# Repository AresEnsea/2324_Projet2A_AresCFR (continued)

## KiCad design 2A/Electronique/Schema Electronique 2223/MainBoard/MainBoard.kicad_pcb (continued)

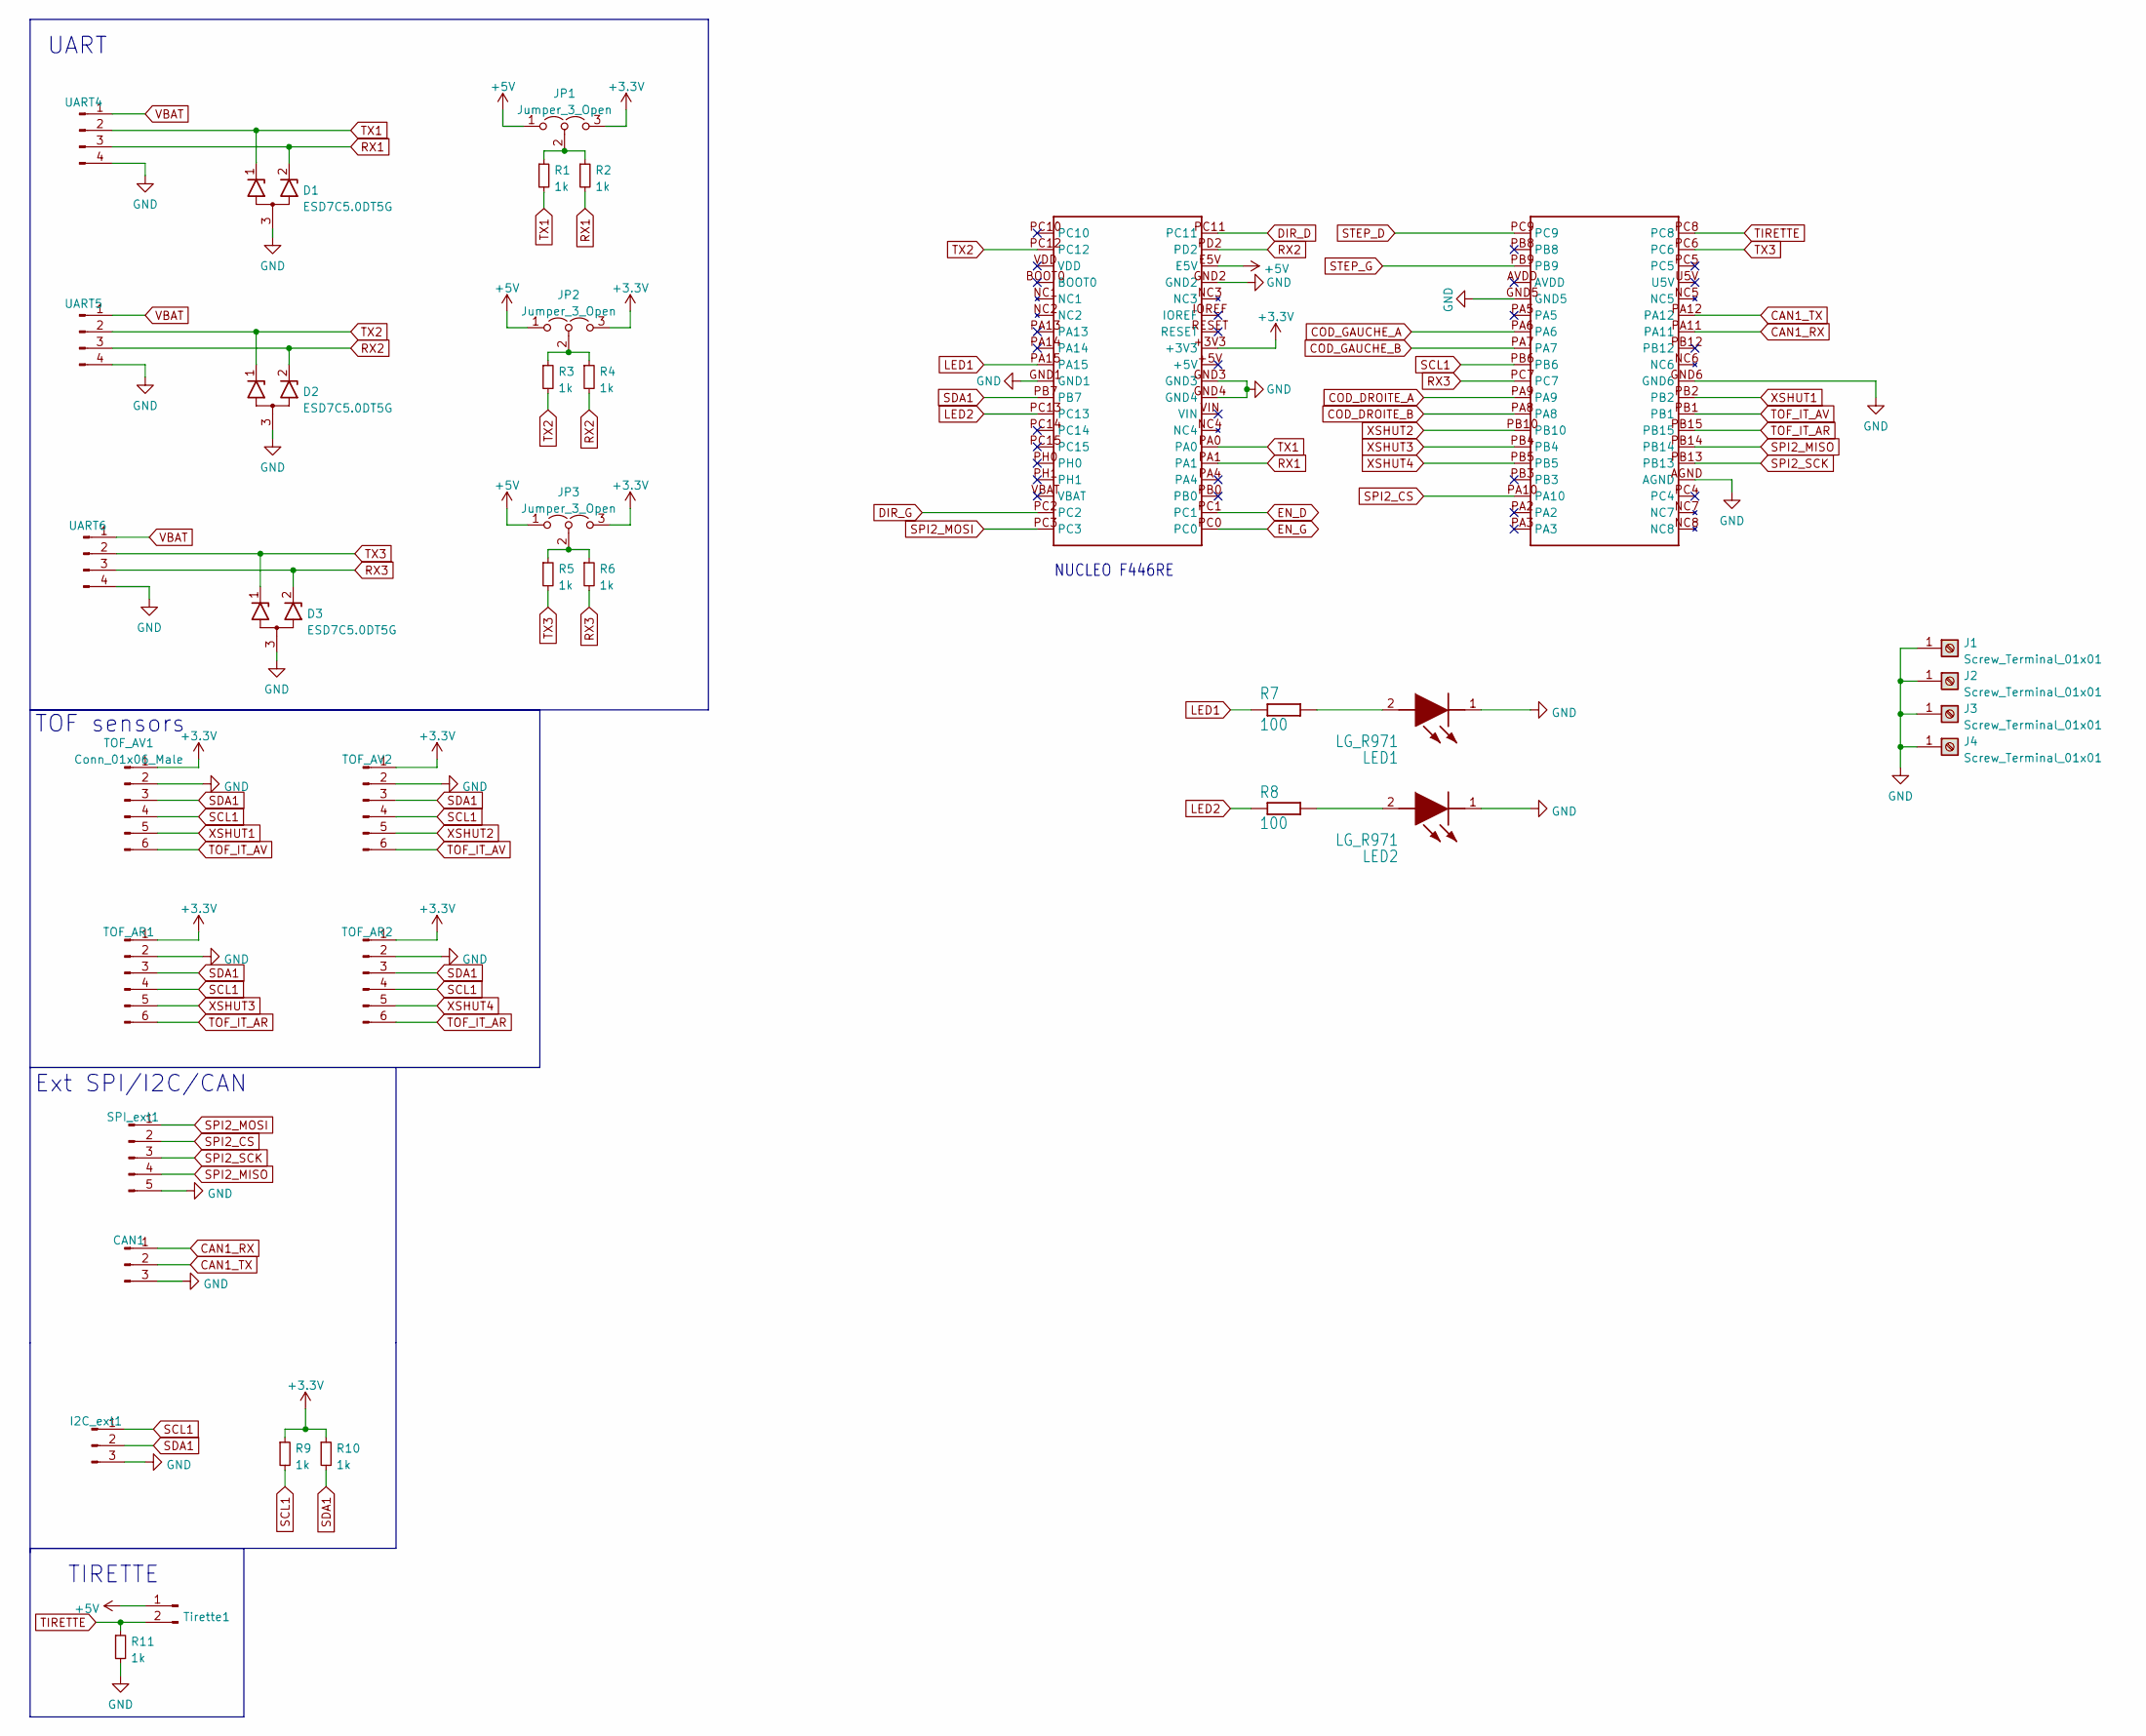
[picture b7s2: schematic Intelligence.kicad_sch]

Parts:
CAN1: Conn_01x03_Male; JST_XH_B3B-XH-A_1x03_P2.50mm_Vertical
D1, D2, D3: ESD7C5.0DT5G; SOT-416; Mouser Part Number 863-ESD7C5.0DT5G
I2C_ext1: Conn_01x03_Male; JST_XH_B3B-XH-A_1x03_P2.50mm_Vertical
J1, J2, J3, J4: Screw_Terminal_01x01; MountingHole_4.3mm_M4_ISO7380_Pad
JP1, JP2, JP3: Jumper_3_Open; PinHeader_1x03_P2.54mm_Vertical
LED1, LED2: LG_R971; LEDC2012X90N
R1, R2, R3, R4, R5, R6, R9, R10, R11: 1k; R_0805_2012Metric_Pad1.20x1.40mm_HandSolder
R7, R8: 100; R0805
SPI_ext1: Conn_01x05_Male; JST_XH_B5B-XH-A_1x05_P2.50mm_Vertical
TOF_AR1, TOF_AR2: Conn_01x06_Male; JST_XH_B6B-XH-A_1x06_P2.50mm_Vertical
TOF_AV1, TOF_AV2: Conn_01x06_Male; JST_XH_B6B-XH-A_1x06_P2.50mm_Vertical
Tirette1: Conn_01x02_Male; PinHeader_1x02_P2.54mm_Vertical
U1: NUCLEO_F446RE; MB1136
UART4, UART5, UART6: Conn_01x04_Male; JST_XH_B4B-XH-A_1x04_P2.50mm_Vertical

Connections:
+3.3V: JP1.3 (B), JP2.3 (B), JP3.3 (B), R9.1, R10.1, TOF_AR1.1, TOF_AR2.1, TOF_AV1.1, TOF_AV2.1, U1.+3V3
+5V: JP1.1 (A), JP2.1 (A), JP3.1 (A), Tirette1.1, U1.E5V; also elsewhere on the board
CAN1_RX: CAN1.1, U1.PA11
CAN1_TX: CAN1.2, U1.PA12
COD_DROITE_A: U1.PA9; also elsewhere on the board
COD_DROITE_B: U1.PA8; also elsewhere on the board
COD_GAUCHE_A: U1.PA6; also elsewhere on the board
COD_GAUCHE_B: U1.PA7; also elsewhere on the board
DIR_D: U1.PC11; also elsewhere on the board
DIR_G: U1.PC2; also elsewhere on the board
EN_D: U1.PC1; also elsewhere on the board
EN_G: U1.PC0; also elsewhere on the board
GND: CAN1.3, D1.3 (A), D2.3 (A), D3.3 (A), I2C_ext1.3, J1.1, J2.1, J3.1, J4.1, LED1.1 (K), LED2.1 (K), R11.2, SPI_ext1.5, TOF_AR1.2, TOF_AR2.2, TOF_AV1.2, TOF_AV2.2, U1.AGND, U1.GND1, U1.GND2, U1.GND3, U1.GND4, U1.GND5, U1.GND6, UART4.4, UART5.4, UART6.4; also elsewhere on the board
LED1: R7.1, U1.PA15
LED2: R8.1, U1.PC13
unnamed: JP1.2 (C), R1.1, R2.1
unnamed: JP2.2 (C), R3.1, R4.1
unnamed: JP3.2 (C), R5.1, R6.1
unnamed: LED1.2 (A), R7.2
unnamed: LED2.2 (A), R8.2
RX1: D1.2 (K2), R2.2, U1.PA1, UART4.3
RX2: D2.2 (K2), R4.2, U1.PD2, UART5.3
RX3: D3.2 (K2), R6.2, U1.PC7, UART6.3
SCL1: I2C_ext1.1, R9.2, TOF_AR1.4, TOF_AR2.4, TOF_AV1.4, TOF_AV2.4, U1.PB6
SDA1: I2C_ext1.2, R10.2, TOF_AR1.3, TOF_AR2.3, TOF_AV1.3, TOF_AV2.3, U1.PB7
SPI2_CS: SPI_ext1.2, U1.PA10
SPI2_MISO: SPI_ext1.4, U1.PB14
SPI2_MOSI: SPI_ext1.1, U1.PC3
SPI2_SCK: SPI_ext1.3, U1.PB13
STEP_D: U1.PC9; also elsewhere on the board
STEP_G: U1.PB9; also elsewhere on the board
TIRETTE: R11.1, Tirette1.2, U1.PC8
TOF_IT_AR: TOF_AR1.6, TOF_AR2.6, U1.PB15
TOF_IT_AV: TOF_AV1.6, TOF_AV2.6, U1.PB1
TX1: D1.1 (K1), R1.2, U1.PA0, UART4.2
TX2: D2.1 (K1), R3.2, U1.PC12, UART5.2
TX3: D3.1 (K1), R5.2, U1.PC6, UART6.2
VBAT: UART4.1, UART5.1, UART6.1; also elsewhere on the board
XSHUT1: TOF_AV1.5, U1.PB2
XSHUT2: TOF_AV2.5, U1.PB10
XSHUT3: TOF_AR1.5, U1.PB4
XSHUT4: TOF_AR2.5, U1.PB5

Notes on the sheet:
UART
NUCLEO F446RE
Ext SPI/I2C/CAN
TOF sensors
TIRETTE

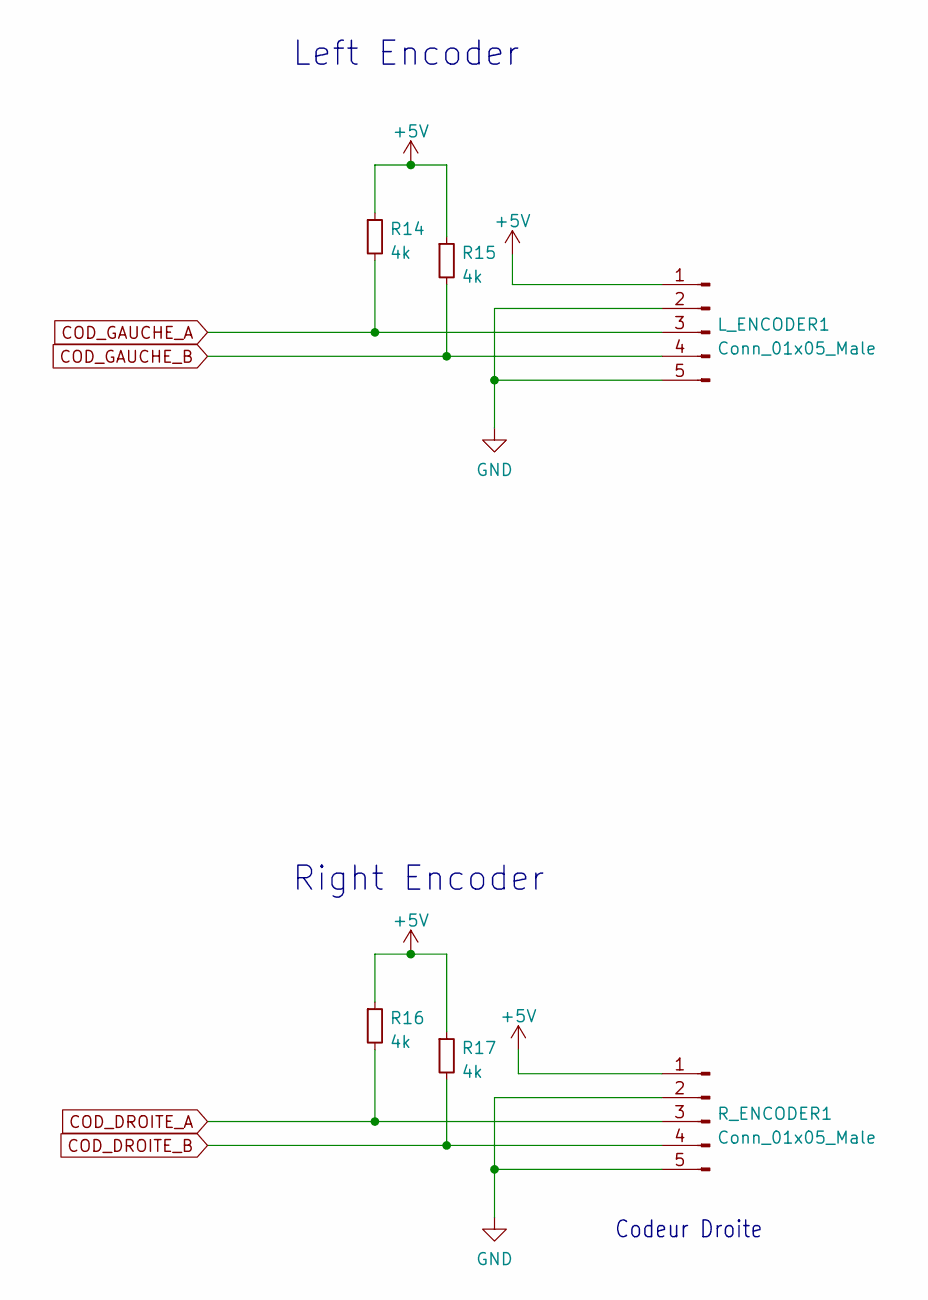
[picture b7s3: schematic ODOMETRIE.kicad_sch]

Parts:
L_ENCODER1: Conn_01x05_Male; JST_XH_B5B-XH-A_1x05_P2.50mm_Vertical
R14, R15, R16, R17: 4k; R_0805_2012Metric_Pad1.20x1.40mm_HandSolder
R_ENCODER1: Conn_01x05_Male; JST_XH_B5B-XH-A_1x05_P2.50mm_Vertical

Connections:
+5V: L_ENCODER1.1, R14.1, R15.1, R16.1, R17.1, R_ENCODER1.1; also elsewhere on the board
COD_DROITE_A: R16.2, R_ENCODER1.3; also elsewhere on the board
COD_DROITE_B: R17.2, R_ENCODER1.4; also elsewhere on the board
COD_GAUCHE_A: L_ENCODER1.3, R14.2; also elsewhere on the board
COD_GAUCHE_B: L_ENCODER1.4, R15.2; also elsewhere on the board
GND: L_ENCODER1.2, L_ENCODER1.5, R_ENCODER1.2, R_ENCODER1.5; also elsewhere on the board

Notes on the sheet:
Codeur Droite
Left Encoder
Right Encoder

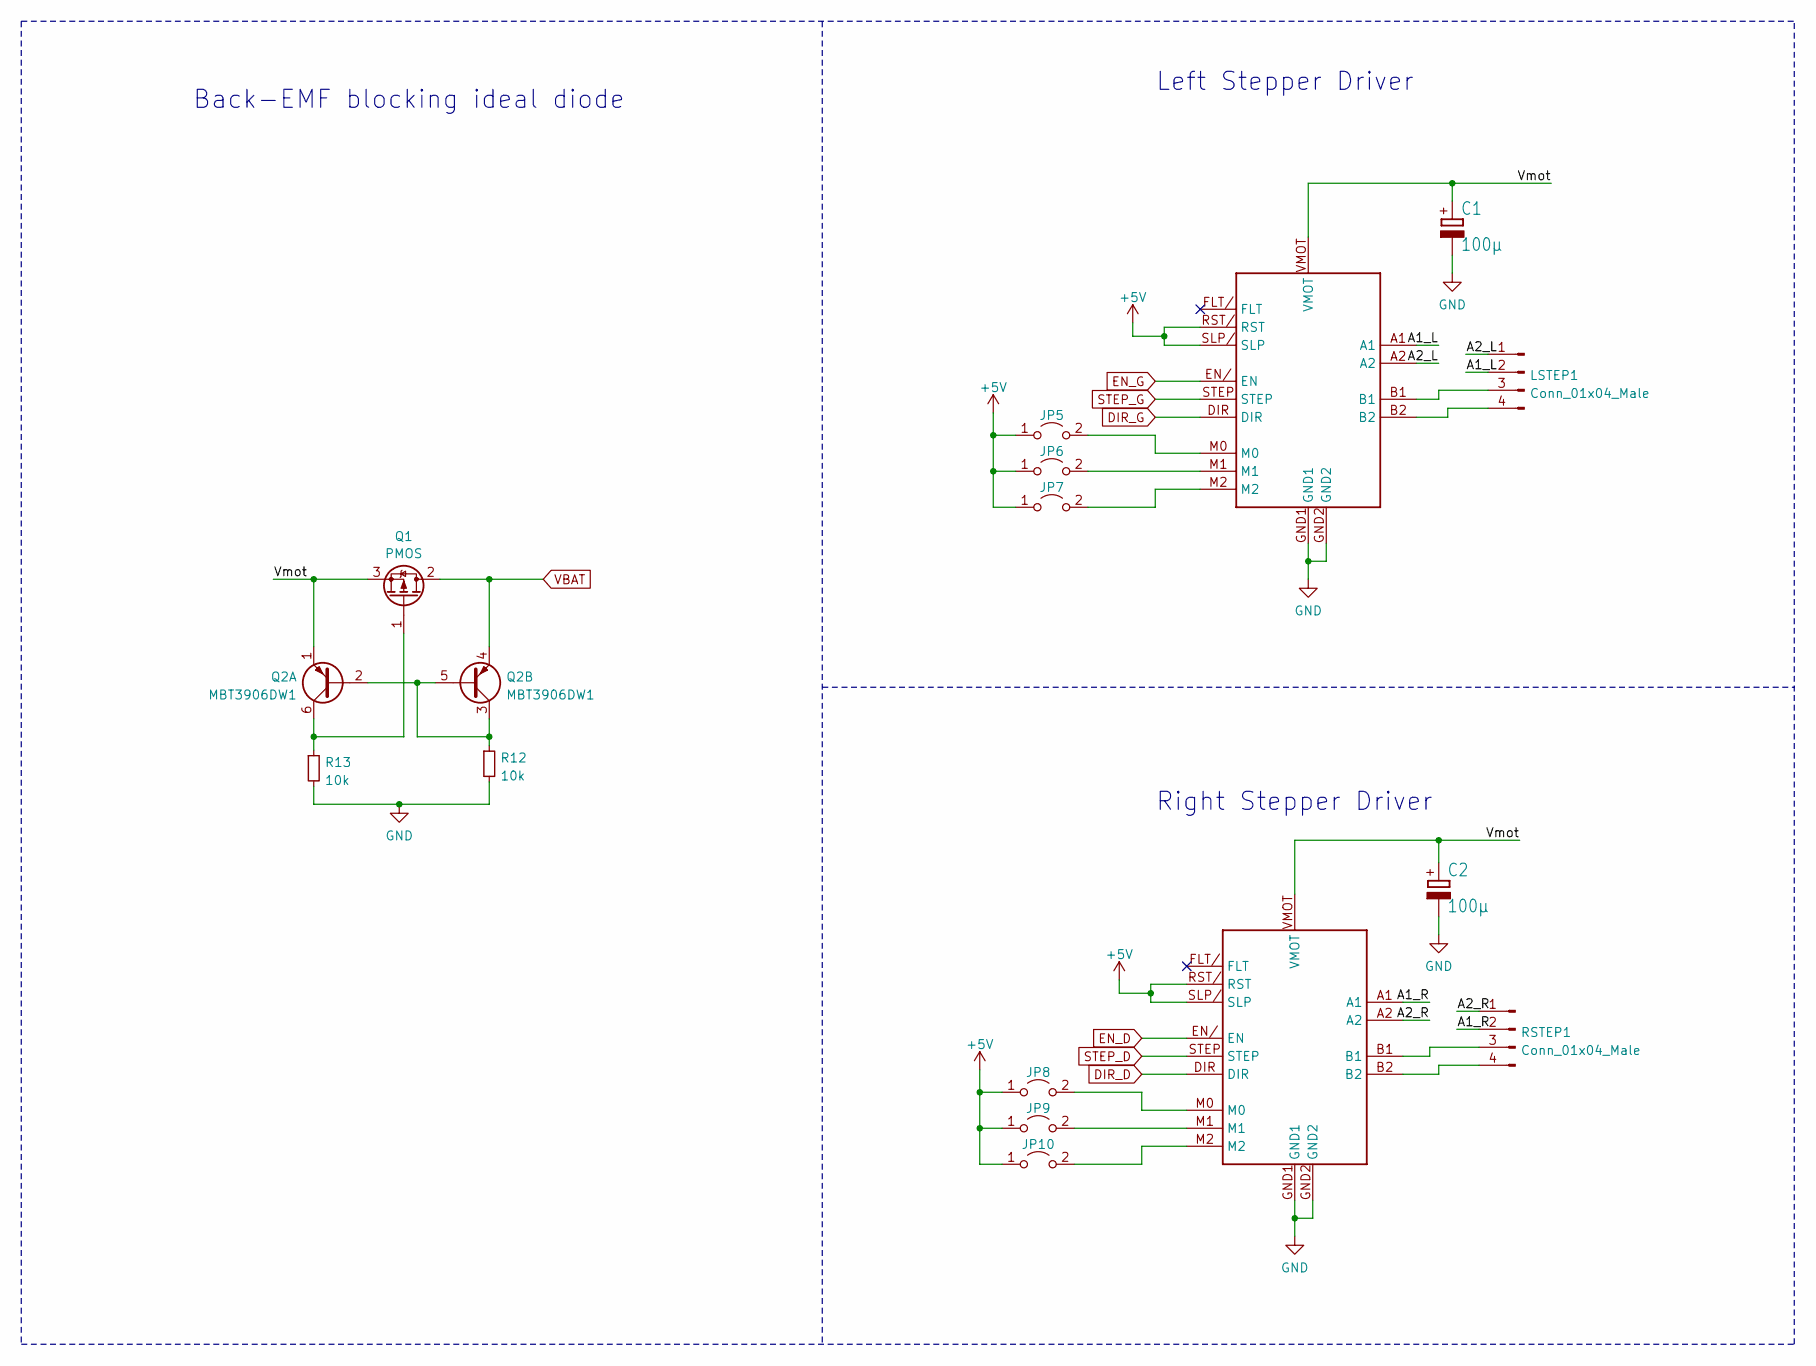
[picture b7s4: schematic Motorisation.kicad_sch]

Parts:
C1, C2: 100µ; E5-6
JP5, JP6, JP7, JP8, JP9, JP10: Jumper_2_Open; PinHeader_1x02_P2.54mm_Vertical
LSTEP1: Conn_01x04_Male; JST_XH_B4B-XH-A_1x04_P2.50mm_Vertical
Q1: PMOS; MOS_WDFN8; Mouser Part Number 863-NTTFS015P03P8ZWG
Q2: MBT3906DW1; SOT-363_SC-70-6; Mouser Part Number 863-MBT3906DW1T1G
R12, R13: 10k; R_0805_2012Metric_Pad1.20x1.40mm_HandSolder
RSTEP1: Conn_01x04_Male; JST_XH_B4B-XH-A_1x04_P2.50mm_Vertical
U2, U3: POLOLU_DRV8825

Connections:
+5V: JP5.1 (A), JP6.1 (A), JP7.1 (A), JP8.1 (A), JP9.1 (A), JP10.1 (A), U2.RST/ (RST), U2.SLP/ (SLP), U3.RST/ (RST), U3.SLP/ (SLP); also elsewhere on the board
/Motorisation/A1_L: LSTEP1.2, U2.A1
/Motorisation/A1_R: RSTEP1.2, U3.A1
/Motorisation/A2_L: LSTEP1.1, U2.A2
/Motorisation/A2_R: RSTEP1.1, U3.A2
/Motorisation/Vmot: C1.+, C2.+, Q1.3 (S), Q2.1 (E1), U2.VMOT, U3.VMOT
DIR_D: U3.DIR; also elsewhere on the board
DIR_G: U2.DIR; also elsewhere on the board
EN_D: U3.EN/ (EN); also elsewhere on the board
EN_G: U2.EN/ (EN); also elsewhere on the board
GND: C1.-, C2.-, R12.2, R13.2, U2.GND1, U2.GND2, U3.GND1, U3.GND2; also elsewhere on the board
unnamed: JP5.2 (B), U2.M0
unnamed: JP6.2 (B), U2.M1
unnamed: JP7.2 (B), U2.M2
unnamed: JP8.2 (B), U3.M0
unnamed: JP9.2 (B), U3.M1
unnamed: JP10.2 (B), U3.M2
unnamed: LSTEP1.3, U2.B1
unnamed: LSTEP1.4, U2.B2
unnamed: Q1.1 (G), Q2.6 (C1), R13.1
unnamed: Q2.2 (B1), Q2.3 (C2), Q2.5 (B2), R12.1
unnamed: RSTEP1.3, U3.B1
unnamed: RSTEP1.4, U3.B2
STEP_D: U3.STEP; also elsewhere on the board
STEP_G: U2.STEP; also elsewhere on the board
VBAT: Q1.2 (D), Q2.4 (E2); also elsewhere on the board

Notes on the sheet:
Back-EMF blocking ideal diode
Right Stepper Driver
Left Stepper Driver

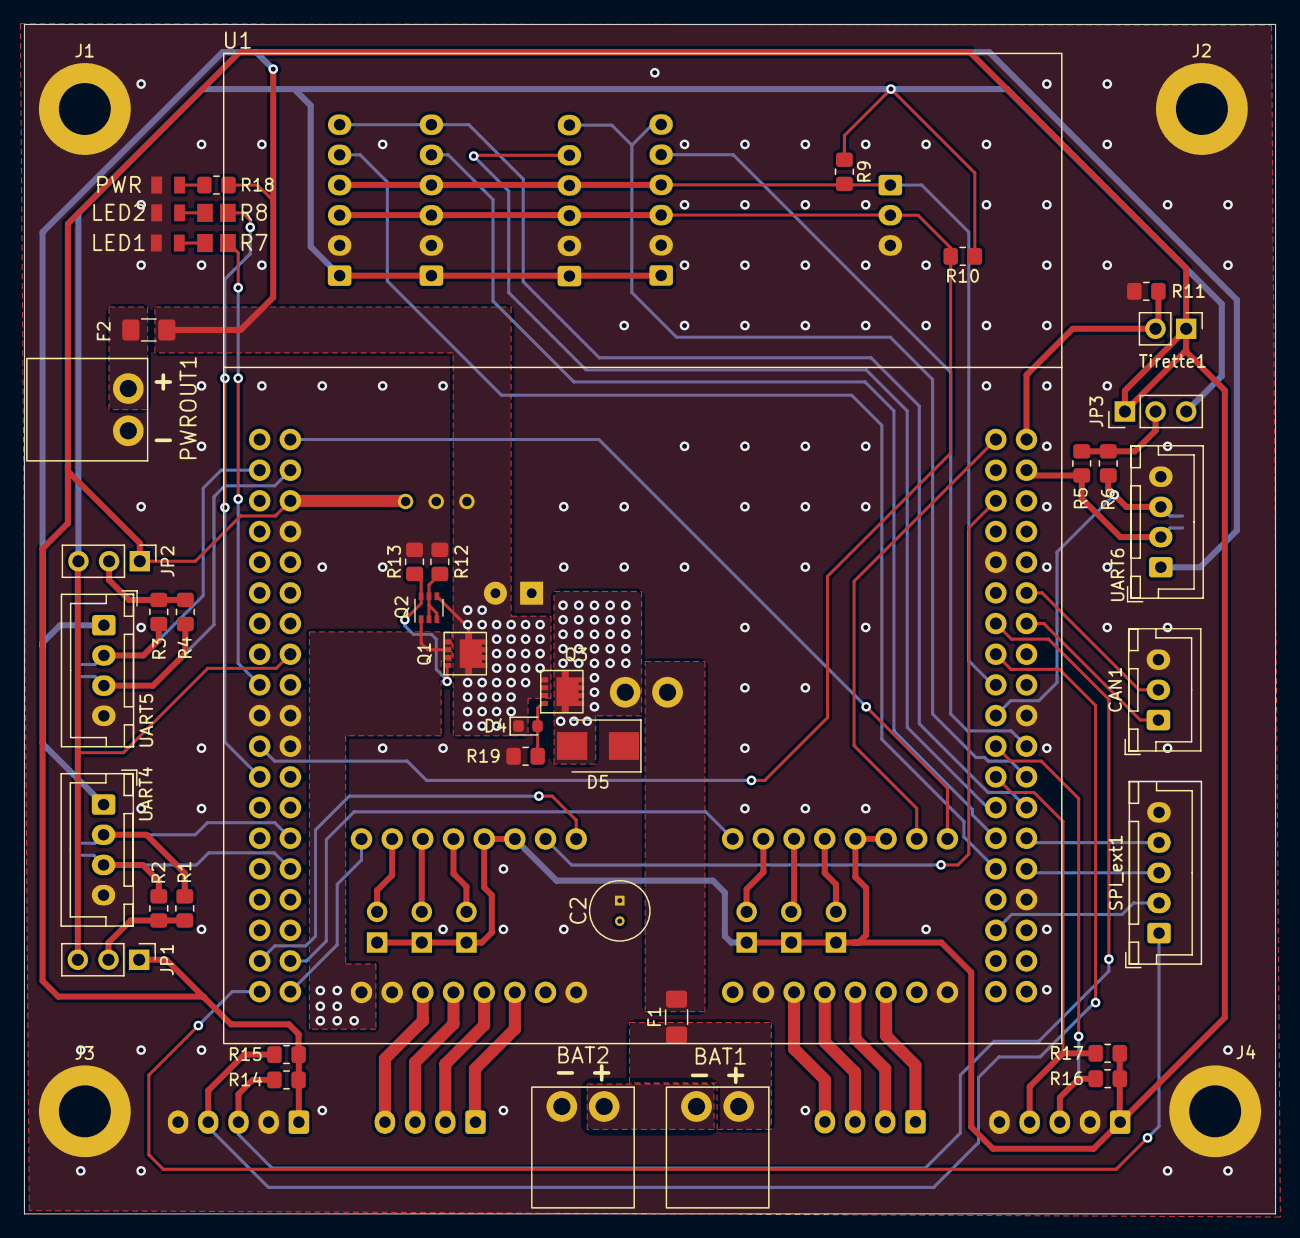
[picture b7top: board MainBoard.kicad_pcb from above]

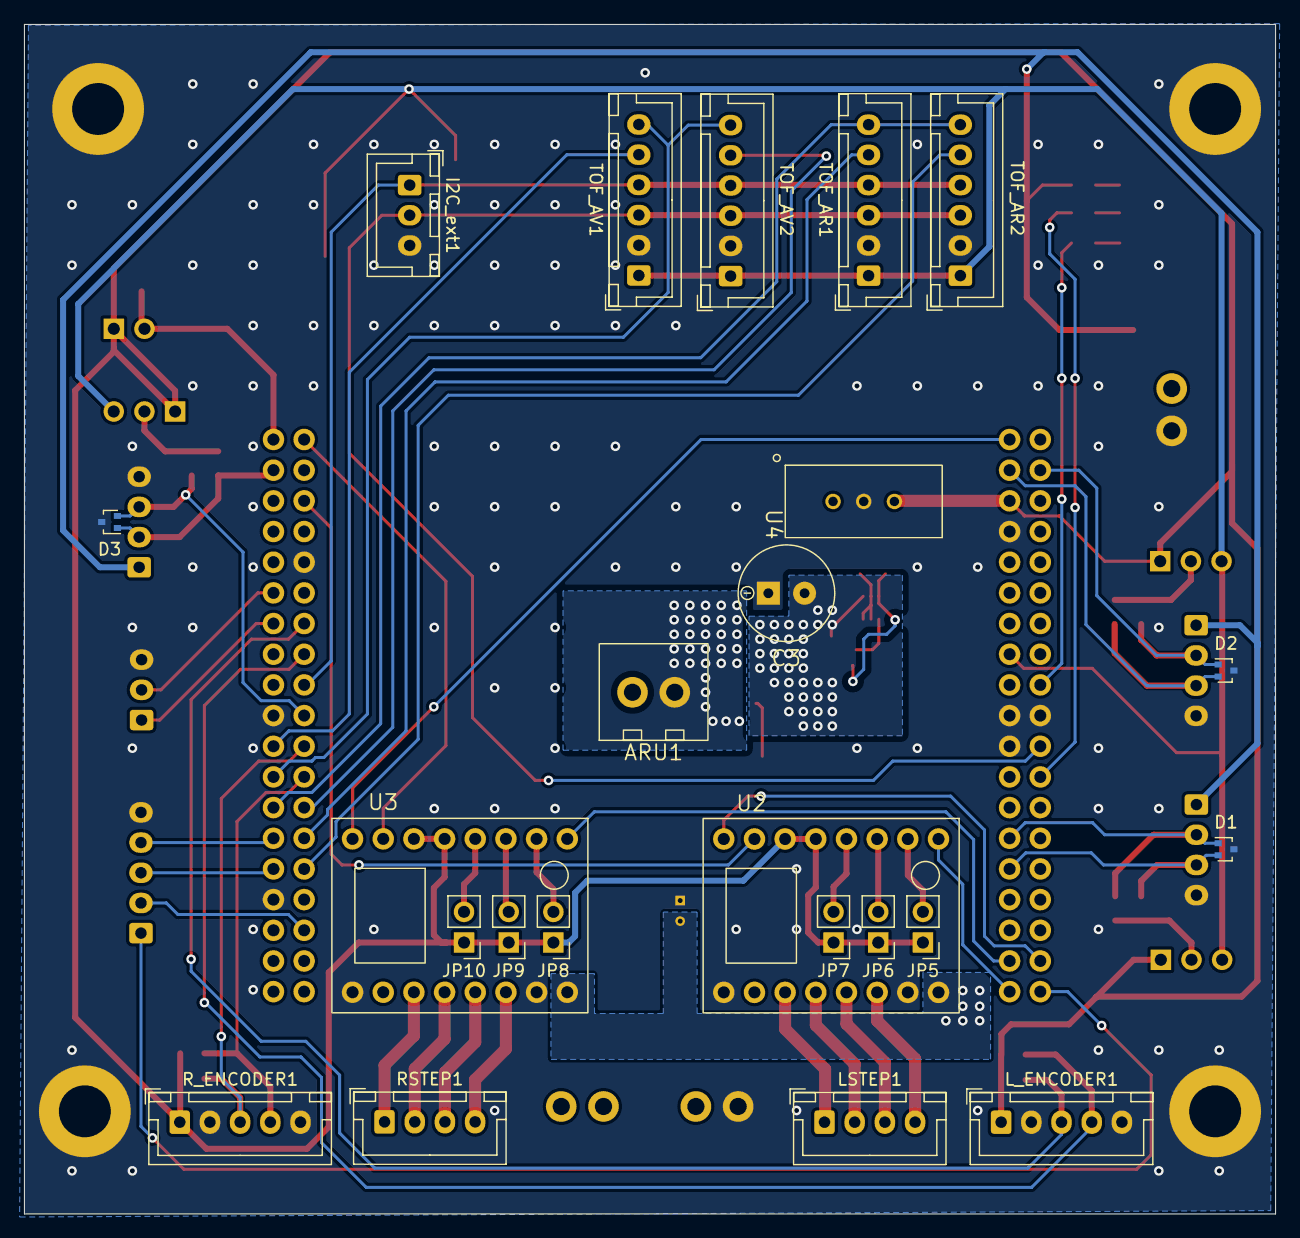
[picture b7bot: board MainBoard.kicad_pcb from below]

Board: 2 copper layers, 103.6 x 98.5 mm, 70 parts (23 on the bottom side), 66 nets.

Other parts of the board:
PWR: LG_R971; LEDC2012X90N

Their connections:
GND: PWR.1 (K); also elsewhere on the board
unnamed 37: PWR.2 (A); also elsewhere on the board

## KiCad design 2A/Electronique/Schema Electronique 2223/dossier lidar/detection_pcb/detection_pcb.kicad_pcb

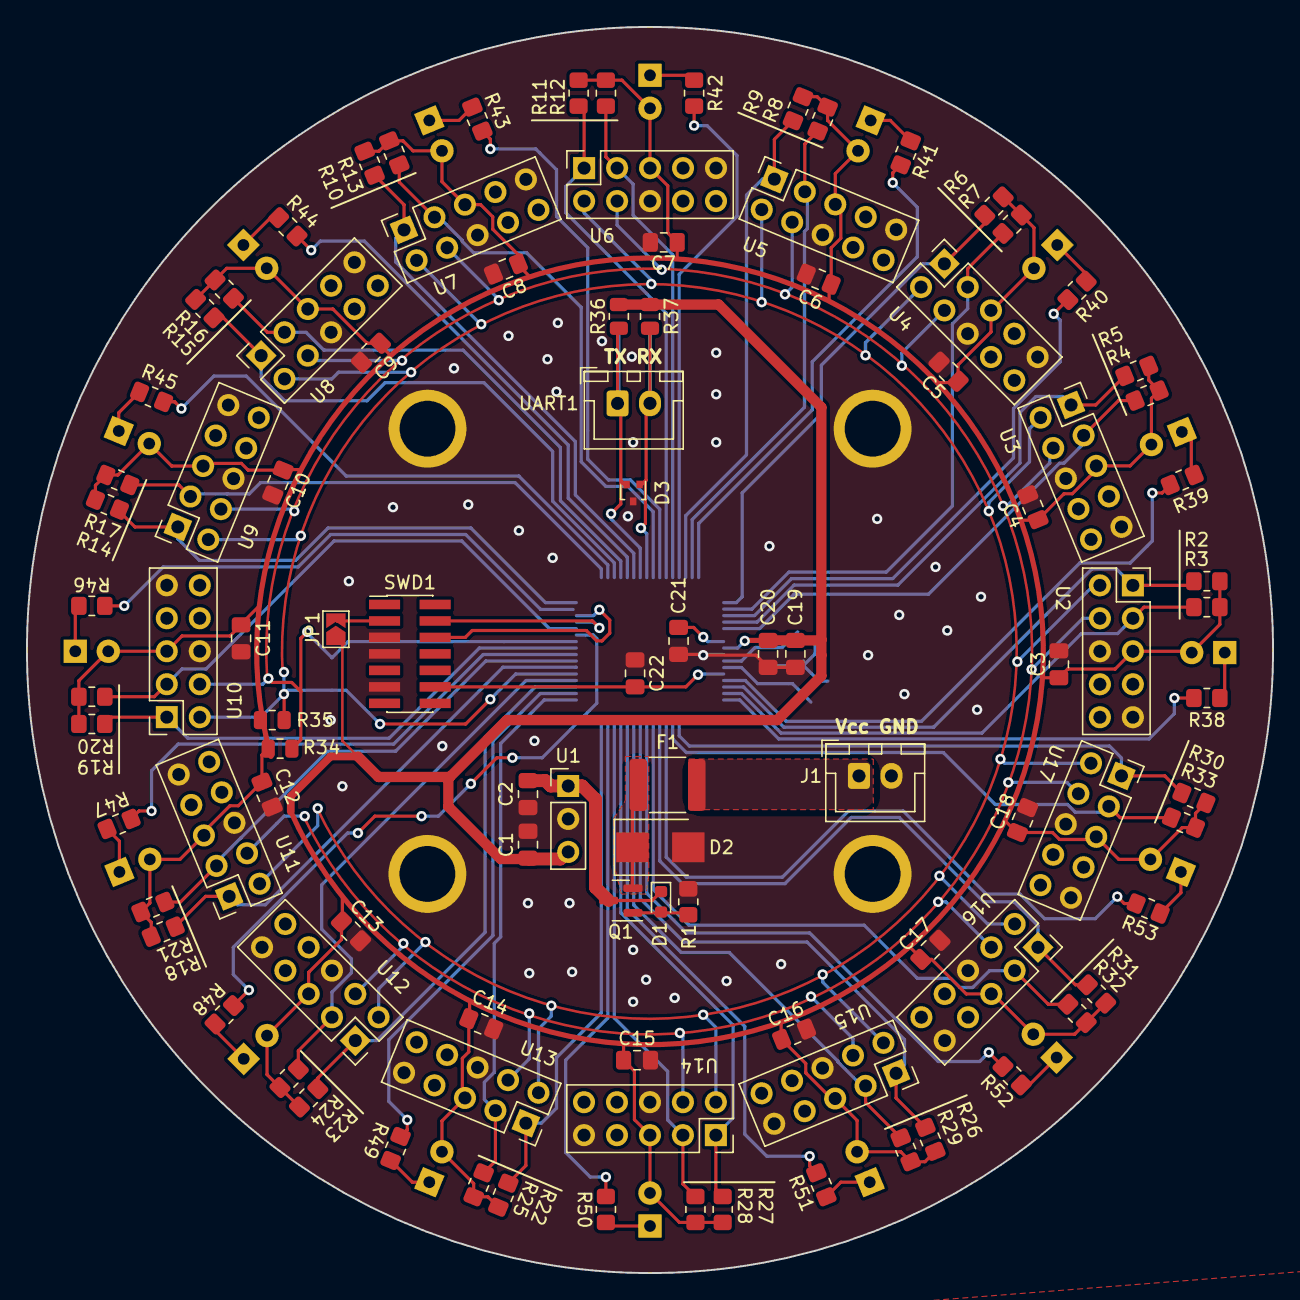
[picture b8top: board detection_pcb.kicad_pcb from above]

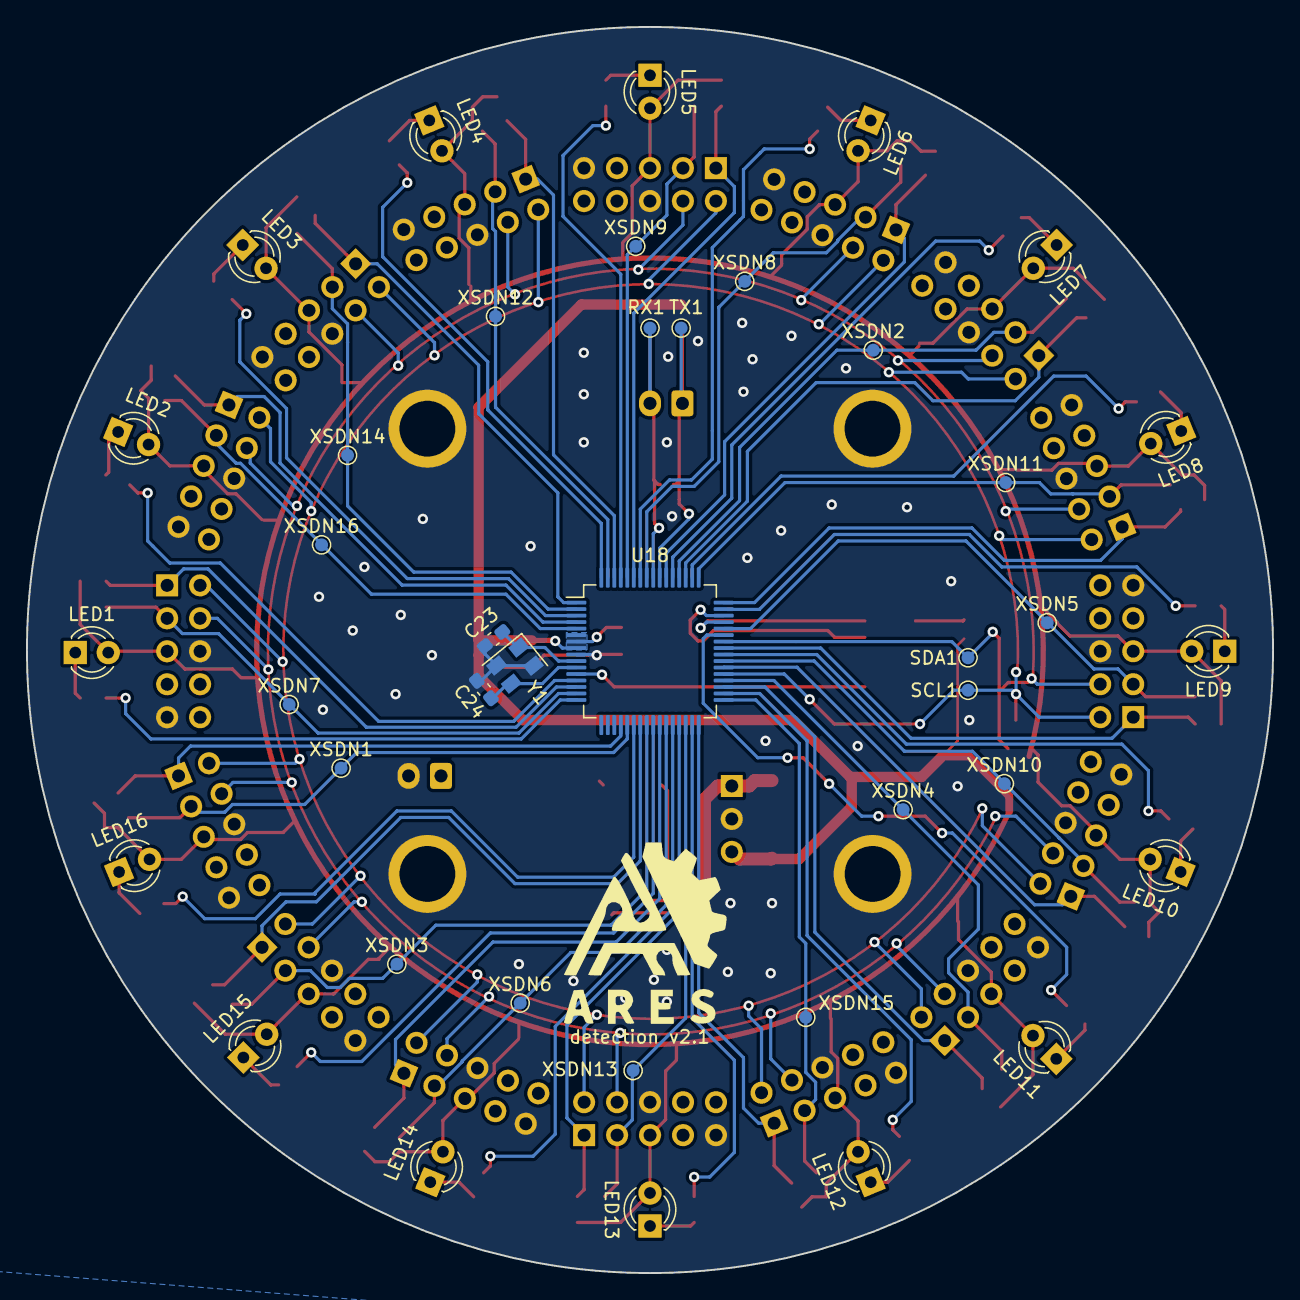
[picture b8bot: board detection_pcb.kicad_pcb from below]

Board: 2 copper layers, 96.0 x 96.0 mm, 145 parts (40 on the bottom side), 80 nets.

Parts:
C1: 10u; C_0805_2012Metric_Pad1.18x1.45mm_HandSolder
C2: 22u; C_0805_2012Metric_Pad1.18x1.45mm_HandSolder
C3, C4, C5, C6, C7, C8, C9, C10, C11, C12, C13, C14, C15, C16, C17, C18: 1u; C_0805_2012Metric_Pad1.18x1.45mm_HandSolder
C19: 4.7u; C_0805_2012Metric_Pad1.18x1.45mm_HandSolder
C20, C21, C22: 100n; C_0805_2012Metric_Pad1.18x1.45mm_HandSolder
C23, C24: 20p; C_0603_1608Metric_Pad1.08x0.95mm_HandSolder
D1: 4V7; D_0603_1608Metric
D2: 1.5SMBJ36CA; D_SMB
D3: ESD7C5.0DT5G; SOT-416
F1: polyfuse; polyswitch
H1, H2, H3, H4: MountingHole_Pad; MountingHole_4.3mm_M4_DIN965_Pad
J1: BAT; JST_XH_B2B-XH-A_1x02_P2.50mm_Vertical
JP1: SolderJumper_2_Open; SolderJumper-2_P1.3mm_Open_TrianglePad1.0x1.5mm
LED1, LED2, LED3, LED4, LED5, LED6, LED7, LED8, LED9, LED10, LED11, LED12, LED13, LED14, LED15, LED16: LED; LED_D3.0mm
Q1: PMOS; SOT-23
R1, R2, R3, R4, R5, R6, R7, R8, R9, R10, R11, R12, R13, R14, R15, R16, R17, R18, R19, R20, R21, R22, R23, R24, R25, R26, R27, R28, R29, R30, R31, R32, R33: 10k; R_0805_2012Metric_Pad1.20x1.40mm_HandSolder
R34, R35: 2.2k; R_0805_2012Metric
R36, R37: DNP; R_0805_2012Metric
R38, R39, R40, R41, R42, R43, R44, R45, R46, R47, R48, R49, R50, R51, R52, R53: 3k; R_0805_2012Metric_Pad1.20x1.40mm_HandSolder
RX1: TestPoint; TestPoint_Pad_D1.0mm
SCL1: TestPoint; TestPoint_Pad_D1.0mm
SDA1: TestPoint; TestPoint_Pad_D1.0mm
SWD1: Conn_02x07_Odd_Even; PinHeader_2x07_P1.27mm_Vertical_SMD
TX1: TestPoint; TestPoint_Pad_D1.0mm
U1: Buck_3.3V; PinHeader_1x03_P2.54mm_Vertical
U2, U3, U4, U5, U6, U7, U8, U9, U10, U11, U12, U13, U14, U15, U16, U17: VL53L1X_module; PinHeader_2x05_P2.54mm_Vertical
U18: STM32G070; LQFP-64_10x10mm_P0.5mm
UART1: Conn_01x02_Male; JST_XH_B2B-XH-A_1x02_P2.50mm_Vertical
XSDN1, XSDN2, XSDN3, XSDN4, XSDN5, XSDN6, XSDN7, XSDN8, XSDN9, XSDN10, XSDN11, XSDN12, XSDN13, XSDN14, XSDN15, XSDN16: TestPoint; TestPoint_Pad_D1.0mm
Y1: 16MHz; Crystal_SMD_EuroQuartz_MT-4Pin_3.2x2.5mm

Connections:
+3V3: C1.1, C3.1, C4.1, C5.1, C6.1, C7.1, C8.1, C9.1, C10.1, C11.1, C12.1, C13.1, C14.1, C15.1, C16.1, C17.1, C18.1, C19.1, C20.1, C21.1, JP1.1 (A), LED1.2 (A), LED2.2 (A), LED3.2 (A), LED4.2 (A), LED5.2 (A), LED6.2 (A), LED7.2 (A), LED8.2 (A), LED9.2 (A), LED10.2 (A), LED11.2 (A), LED12.2 (A), LED13.2 (A), LED14.2 (A), LED15.2 (A), LED16.2 (A), R2.2, R3.2, R4.2, R5.2, R6.2, R7.2, R8.2, R9.2, R10.2, R11.2, R12.2, R13.2, R14.2, R15.2, R16.2, R17.2, R18.2, R19.2, R20.2, R21.2, R22.2, R23.2, R24.2, R25.2, R26.2, R27.2, R28.2, R29.2, R30.2, R31.2, R32.2, R33.2, R34.1, R35.2, R36.1, R37.1, U1.3 (VOUT), U2.5 (VDD), U3.5 (VDD), U4.5 (VDD), U5.5 (VDD), U6.5 (VDD), U7.5 (VDD), U8.5 (VDD), U9.5 (VDD), U10.5 (VDD), U11.5 (VDD), U12.5 (VDD), U13.5 (VDD), U14.5 (VDD), U15.5 (VDD), U16.5 (VDD), U17.5 (VDD), U18.6 (VBAT), U18.7 (VREF+), U18.8 (VDD/VDDA)
GND: C1.2, C2.2, C3.2, C4.2, C5.2, C6.2, C7.2, C8.2, C9.2, C10.2, C11.2, C12.2, C13.2, C14.2, C15.2, C16.2, C17.2, C18.2, C19.2, C20.2, C21.2, C22.1, C23.2, C24.2, D2.2 (A2), D3.3 (A), H1.1, H2.1, H3.1, H4.1, J1.2, R1.2, SWD1.5, SWD1.7, SWD1.11, U1.2 (GND), U2.6 (GND), U2.9 (NC1), U3.6 (GND), U3.9 (NC1), U4.6 (GND), U4.9 (NC1), U5.6 (GND), U5.9 (NC1), U6.6 (GND), U6.9 (NC1), U7.6 (GND), U7.9 (NC1), U8.6 (GND), U8.9 (NC1), U9.6 (GND), U9.9 (NC1), U10.6 (GND), U10.9 (NC1), U11.6 (GND), U11.9 (NC1), U12.6 (GND), U12.9 (NC1), U13.6 (GND), U13.9 (NC1), U14.6 (GND), U14.9 (NC1), U15.6 (GND), U15.9 (NC1), U16.6 (GND), U16.9 (NC1), U17.6 (GND), U17.9 (NC1), U18.9 (VSS/VSSA), Y1.2, Y1.4
INT0: R2.1, U2.1 (INT), U18.14 (PC1)
INT1: R5.1, U3.1 (INT), U18.4 (PC14)
INT2: R6.1, U4.1 (INT), U18.1 (PC11)
INT3: R9.1, U5.1 (INT), U18.62 (PB8)
INT4: R11.1, U6.1 (INT), U18.59 (PB5)
INT5: R10.1, U7.1 (INT), U18.54 (PD4)
INT6: R15.1, U8.1 (INT), U18.51 (PD1)
INT7: R14.1, U9.1 (INT), U18.48 (PC8)
INT8: R19.1, U10.1 (INT), U18.41 (PD9)
INT9: R18.1, U11.1 (INT), U18.38 (PC6)
INT10: R23.1, U12.1 (INT), U18.35 (PB15)
INT11: R22.1, U13.1 (INT), U18.32 (PB12)
INT12: R27.1, U14.1 (INT), U18.29 (PB2)
INT13: R26.1, U15.1 (INT), U18.26 (PC5)
INT14: R31.1, U16.1 (INT), U18.23 (PA6)
INT15: R30.1, U17.1 (INT), U18.20 (PA3)
LED0: R38.1, U18.16 (PC3)
LED1: R39.2, U18.13 (PC0)
LED2: R40.2, U18.3 (PC13)
LED3: R41.2, U18.64 (PC10)
LED4: R42.2, U18.61 (PB7)
LED5: R43.2, U18.58 (PB4)
LED6: R44.2, U18.53 (PD3)
LED7: R45.2, U18.50 (PD0)
LED8: R46.2, U18.47 (PA15)
LED9: R47.2, U18.40 (PD8)
LED10: R48.2, U18.43 (PA11)
LED11: R49.2, U18.34 (PB14)
LED12: R50.2, U18.31 (PB11)
LED13: R51.2, U18.28 (PB1)
LED14: R52.2, U18.25 (PC4)
LED15: R53.2, U18.22 (PA5)
NRST: C22.2, SWD1.12, U18.12 (NRST)
unnamed: D1.2 (A), Q1.1 (G), R1.1
unnamed: C2.1, D1.1 (K), Q1.3 (S), U1.1 (VIN)
unnamed: D2.1 (A1), F1.1, Q1.2 (D)
unnamed: F1.2, J1.1
unnamed: JP1.2 (B), SWD1.3
unnamed: LED1.1 (K), R38.2
unnamed: LED2.1 (K), R39.1
unnamed: LED3.1 (K), R40.1
unnamed: LED4.1 (K), R41.1
unnamed: LED5.1 (K), R42.1
unnamed: LED6.1 (K), R43.1
unnamed: LED7.1 (K), R44.1
unnamed: LED8.1 (K), R45.1
unnamed: LED9.1 (K), R46.1
unnamed: LED10.1 (K), R47.1
unnamed: LED11.1 (K), R48.1
unnamed: LED12.1 (K), R49.1
unnamed: LED13.1 (K), R50.1
unnamed: LED14.1 (K), R51.1
unnamed: LED15.1 (K), R52.1
unnamed: LED16.1 (K), R53.1
unnamed: C23.1, U18.10 (PF0), Y1.1
unnamed: C24.1, U18.11 (PF1), Y1.3
RX: D3.1 (K), R37.2, RX1.1, U18.56 (PD6), UART1.2
SCL: R35.1, SCL1.1, U2.2 (SCL), U3.2 (SCL), U4.2 (SCL), U5.2 (SCL), U6.2 (SCL), U7.2 (SCL), U8.2 (SCL), U9.2 (SCL), U10.2 (SCL), U11.2 (SCL), U12.2 (SCL), U13.2 (SCL), U14.2 (SCL), U15.2 (SCL), U16.2 (SCL), U17.2 (SCL), U18.37 (PA9)
SDA: R34.2, SDA1.1, U2.4 (SDA), U3.4 (SDA), U4.4 (SDA), U5.4 (SDA), U6.4 (SDA), U7.4 (SDA), U8.4 (SDA), U9.4 (SDA), U10.4 (SDA), U11.4 (SDA), U12.4 (SDA), U13.4 (SDA), U14.4 (SDA), U15.4 (SDA), U16.4 (SDA), U17.4 (SDA), U18.42 (PA10)
SWCLK: SWD1.6, U18.46 (BOOT0-PA14)
SWDIO: SWD1.4, U18.45 (PA13)
TX: D3.2 (K), R36.2, TX1.1, U18.55 (PD5), UART1.1
XSDN1: R3.1, U2.3 (XSDN), U18.15 (PC2), XSDN7.1
XSDN2: R4.1, U3.3 (XSDN), U18.5 (PC15), XSDN16.1
XSDN3: R7.1, U4.3 (XSDN), U18.2 (PC12), XSDN14.1
XSDN4: R8.1, U5.3 (XSDN), U18.63 (PB9), XSDN12.1
XSDN5: R12.1, U6.3 (XSDN), U18.60 (PB6), XSDN9.1
XSDN6: R13.1, U7.3 (XSDN), U18.57 (PB3), XSDN8.1
XSDN7: R16.1, U8.3 (XSDN), U18.52 (PD2), XSDN2.1
XSDN8: R17.1, U9.3 (XSDN), U18.49 (PC9), XSDN11.1
XSDN9: R20.1, U10.3 (XSDN), U18.44 (PA12), XSDN5.1
XSDN10: R21.1, U11.3 (XSDN), U18.39 (PC7), XSDN10.1
XSDN11: R24.1, U12.3 (XSDN), U18.36 (PA8), XSDN4.1
XSDN12: R25.1, U13.3 (XSDN), U18.33 (PB13), XSDN15.1
XSDN13: R28.1, U14.3 (XSDN), U18.30 (PB10), XSDN13.1
XSDN14: R29.1, U15.3 (XSDN), U18.27 (PB0), XSDN6.1
XSDN15: R32.1, U16.3 (XSDN), U18.24 (PA7), XSDN3.1
XSDN16: R33.1, U17.3 (XSDN), U18.21 (PA4), XSDN1.1
